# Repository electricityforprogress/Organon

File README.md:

# Organon
Biodata for Eurorack

This device can connect to the leaves of a plant and produces three pairs of Note CV and Gate signals, along with outputs for the 'raw' PWM Biodata square wave, a 'wiggly' CV output, and MIDI out!  The Organon comes with a set of snap electrode leads and three pairs of sticky pads. 
Using an Arduino Pro Micro 32u4, LMC555 timer, and a MC4728 Quad DAC this device was quite hard to find parts for until late 2023.

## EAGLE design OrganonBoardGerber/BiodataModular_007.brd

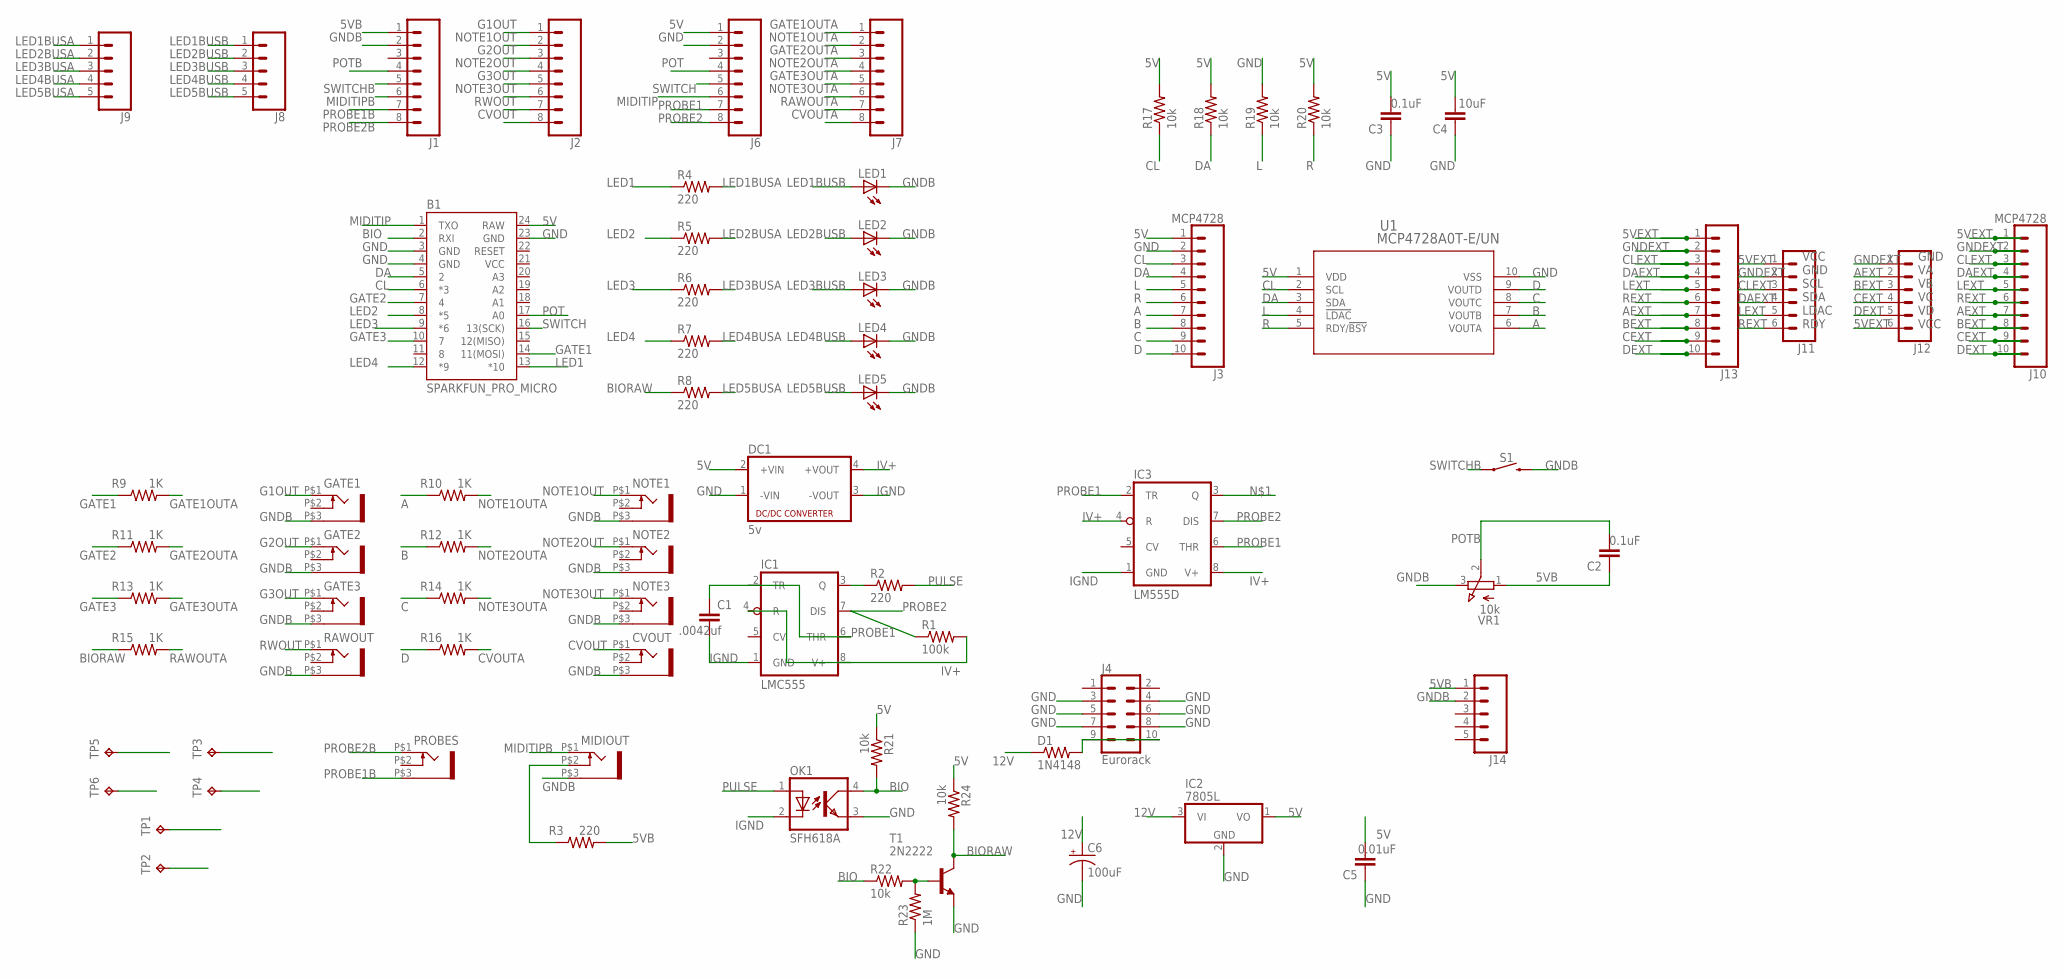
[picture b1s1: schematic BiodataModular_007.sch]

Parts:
B1: SPARKFUN_PRO_MICRO
C1: .0042uf; C2.5-2
C2, C3: 0.1uF; C2.5-2
C4: 10uF; C2.5-2
C5: 0.01uF; C2.5-2
C6: 100uF; B45181A
CVOUT: WQP-PJ301M-12_JACK
D1: 1N4148; 0204V
DC1: 5v; NME
GATE1, GATE2, GATE3: WQP-PJ301M-12_JACK
IC1: LMC555; DIL08
IC2: 7805L; TO92
IC3: LM555D; SO08
J1, J2, J6, J7: CONN_08"; 1X08
J3, J10: MCP4728; 1X10
J4: Eurorack; 2X5
J8, J9, J14: CONN_05; 1X05
J11, J12: CONN_06SILK_FEMALE_PTH; 1X06
J13: CONN_10SMD_MALE; 1X10_SMD_MALE
LED1, LED2, LED3, LED4, LED5: LED3MM
MIDIOUT: WQP-PJ301M-12_JACK
NOTE1, NOTE2, NOTE3: WQP-PJ301M-12_JACK
OK1: SFH618A; DIP4
PROBES: WQP-PJ301M-12_JACK
R1: 100k; 0204V
R2, R3, R4, R5, R6, R7, R8: 220; 0204V
R9, R10, R11, R12, R13, R14, R15, R16: 1K; 0204V
R17, R18, R19, R20, R21, R22, R24: 10k; 0204V
R23: 1M; 0204V
RAWOUT: WQP-PJ301M-12_JACK
S1: MOMENTARY-SWITCH-SPST-PTH-6.0MM; TACTILE_SWITCH_PTH_6.0MM
T1: 2N2222; TO92-EBC-OVAL
TP1, TP2, TP3, TP4, TP5, TP6: TPB1,27; B1,27
U1: MCP4728A0T-E/UN; MSOP10_MC
VR1: 10k; EVUF

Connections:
5V: B1.24 (RAW), C3.2, C4.2, C5.2, DC1.2 (+VIN), IC2.1 (VO), J3.1, J6.1, R17.2, R18.2, R20.2, R21.1, R24.1, U1.1 (VDD)
5VB: C2.1, J1.1, J14.1, R3.2, VR1.1 (A)
5VEXT: J10.1, J11.1, J12.6, J13.1
12V: C6.+, D1.1, IC2.3 (VI)
A: J3.7, R10.1, U1.6 (VOUTA)
AEXT: J10.7, J12.2, J13.7
B: J3.8, R12.1, U1.7 (VOUTB)
BEXT: J10.8, J12.3, J13.8
BIO: B1.2 (RXI), OK1.4 (COL), R21.2, R22.1
BIORAW: R8.1, R15.1, R24.2, T1.C
C: J3.9, R14.1, U1.8 (VOUTC)
CEXT: J10.9, J12.4, J13.9
CL: B1.6 (*3), J3.3, R17.1, U1.2 (SCL)
CLEXT: J10.3, J11.3, J13.3
CVOUT: CVOUT.P$1 (2), J2.8
CVOUTA: J7.8, R16.2
D: J3.10, R16.1, U1.9 (VOUTD)
DA: B1.5 (2), J3.4, R18.1, U1.3 (SDA)
DAEXT: J10.4, J11.4, J13.4
DEXT: J10.10, J12.5, J13.10
G1OUT: GATE1.P$1 (2), J2.1
G2OUT: GATE2.P$1 (2), J2.3
G3OUT: GATE3.P$1 (2), J2.5
GATE1: B1.14 (11(MOSI)), R9.1
GATE1OUTA: J7.1, R9.2
GATE2: B1.7 (4), R11.1
GATE2OUTA: J7.3, R11.2
GATE3: B1.10 (7), R13.1
GATE3OUTA: J7.5, R13.2
GND: B1.3 (GND), B1.4 (GND), B1.23 (GND), C3.1, C4.1, C5.1, C6.-, DC1.1 (-VIN), IC2.2 (GND), J3.2, J4.3, J4.4, J4.5, J4.6, J4.7, J4.8, J6.2, OK1.3 (EMIT), R19.2, R23.1, T1.E, U1.10 (VSS)
GNDB: CVOUT.P$3 (1), GATE1.P$3 (1), GATE2.P$3 (1), GATE3.P$3 (1), J1.2, J14.2, LED1.K (C), LED2.K (C), LED3.K (C), LED4.K (C), LED5.K (C), MIDIOUT.P$3 (1), NOTE1.P$3 (1), NOTE2.P$3 (1), NOTE3.P$3 (1), RAWOUT.P$3 (1), S1.3 (2), VR1.3 (E)
GNDEXT: J10.2, J11.2, J12.1, J13.2
IGND: C1.2, DC1.3 (-VOUT), IC1.1 (GND), IC3.1 (GND), OK1.2 (C)
IV+: DC1.4 (+VOUT), IC1.4 (R), IC1.8 (V+), IC3.4 (R), IC3.8 (V+), R1.2
L: J3.5, R19.1, U1.4 (!LDAC)
LED1: B1.13 (*10), R4.1
LED1BUSA: J9.1, R4.2
LED1BUSB: J8.1, LED1.A
LED2: B1.8 (*5), R5.1
LED2BUSA: J9.2, R5.2
LED2BUSB: J8.2, LED2.A
LED3: B1.9 (*6), R6.1
LED3BUSA: J9.3, R6.2
LED3BUSB: J8.3, LED3.A
LED4: B1.12 (*9), R7.1
LED4BUSA: J9.4, R7.2
LED4BUSB: J8.4, LED4.A
LED5BUSA: J9.5, R8.2
LED5BUSB: J8.5, LED5.A
LEXT: J10.5, J11.5, J13.5
MIDITIP: B1.1 (TXO), J6.6
MIDITIPB: J1.6, MIDIOUT.P$1 (2)
unnamed: IC1.3 (Q), IC3.3 (Q), R2.1
unnamed: MIDIOUT.P$2 (3), R3.1
unnamed: D1.2, J4.9, J4.10
unnamed: R22.2, R23.2, T1.B
NOTE1OUT: J2.2, NOTE1.P$1 (2)
NOTE1OUTA: J7.2, R10.2
NOTE2OUT: J2.4, NOTE2.P$1 (2)
NOTE2OUTA: J7.4, R12.2
NOTE3OUT: J2.6, NOTE3.P$1 (2)
NOTE3OUTA: J7.6, R14.2
POT: B1.17 (A0), J6.4
POTB: C2.2, J1.4, VR1.2 (S)
PROBE1: C1.1, IC1.2 (TR), IC1.6 (THR), IC3.2 (TR), IC3.6 (THR), J6.7
PROBE1B: J1.7, PROBES.P$3 (1), TP2.TP
PROBE1C: TP4.TP
PROBE1C1: TP6.TP
PROBE2: IC1.7 (DIS), IC3.7 (DIS), J6.8, R1.1
PROBE2B: J1.8, PROBES.P$1 (2), TP1.TP
PROBE2C: TP3.TP
PROBE2C1: TP5.TP
PULSE: OK1.1 (A), R2.2
R: J3.6, R20.1, U1.5 (RDY/!BSY)
RAWOUTA: J7.7, R15.2
REXT: J10.6, J11.6, J13.6
RWOUT: J2.7, RAWOUT.P$1 (2)
SWITCH: B1.16 (13(SCK)), J6.5
SWITCHB: J1.5, S1.1
VCC: B1.21 (VCC)

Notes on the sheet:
VCC GND SCL SDA LDAC RDY
GND VA VB VC VD VCC

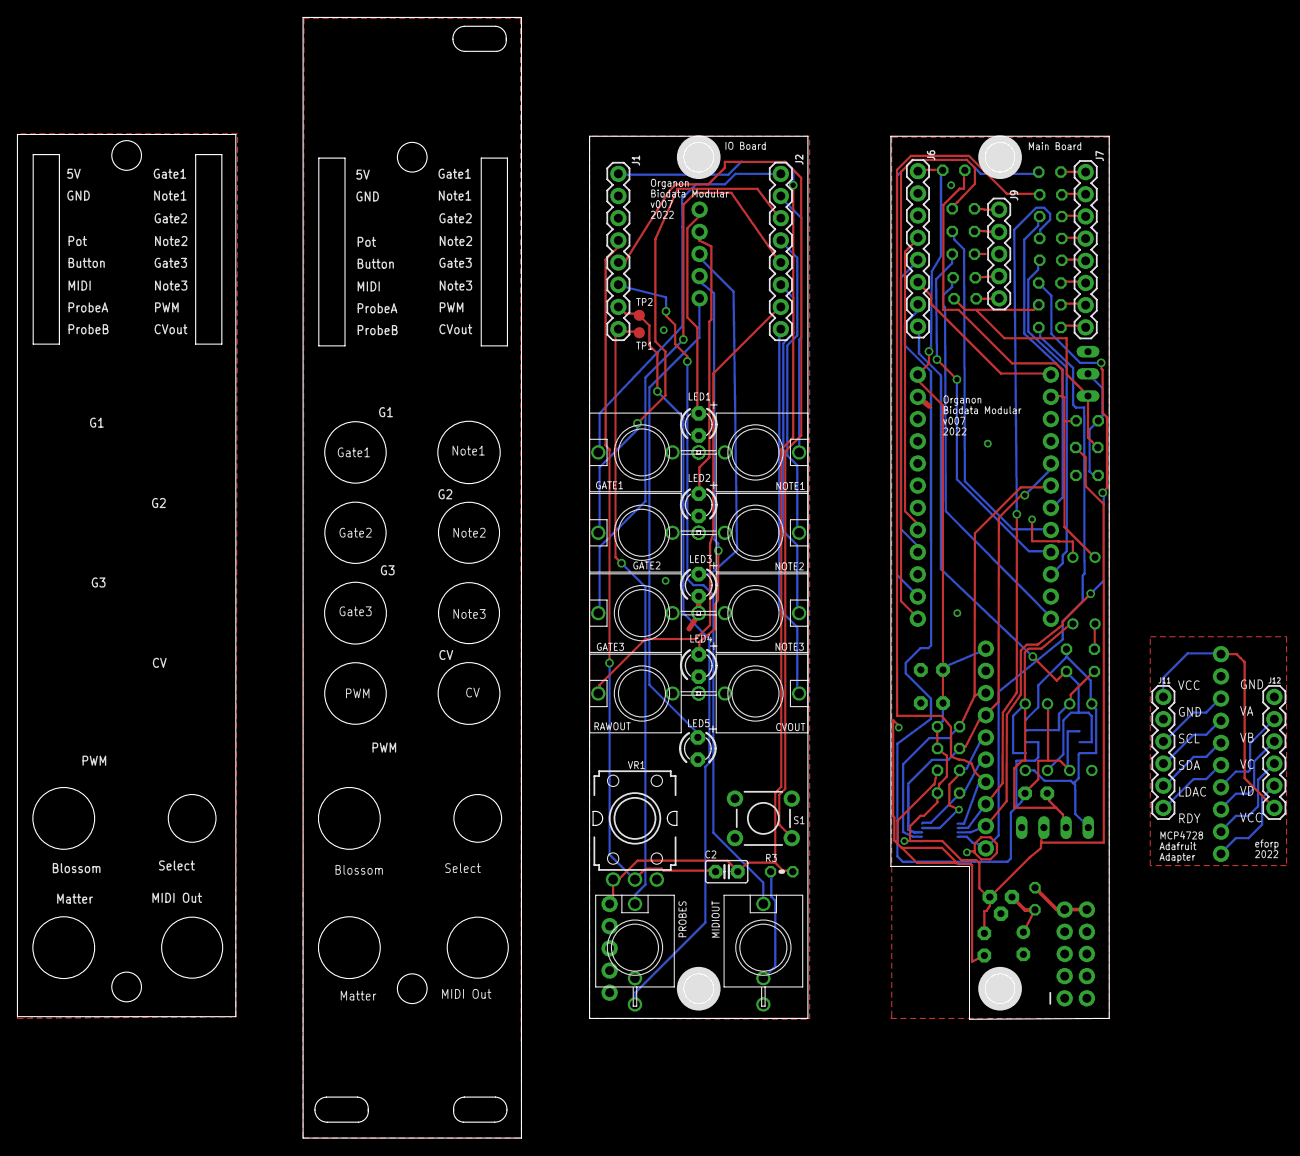
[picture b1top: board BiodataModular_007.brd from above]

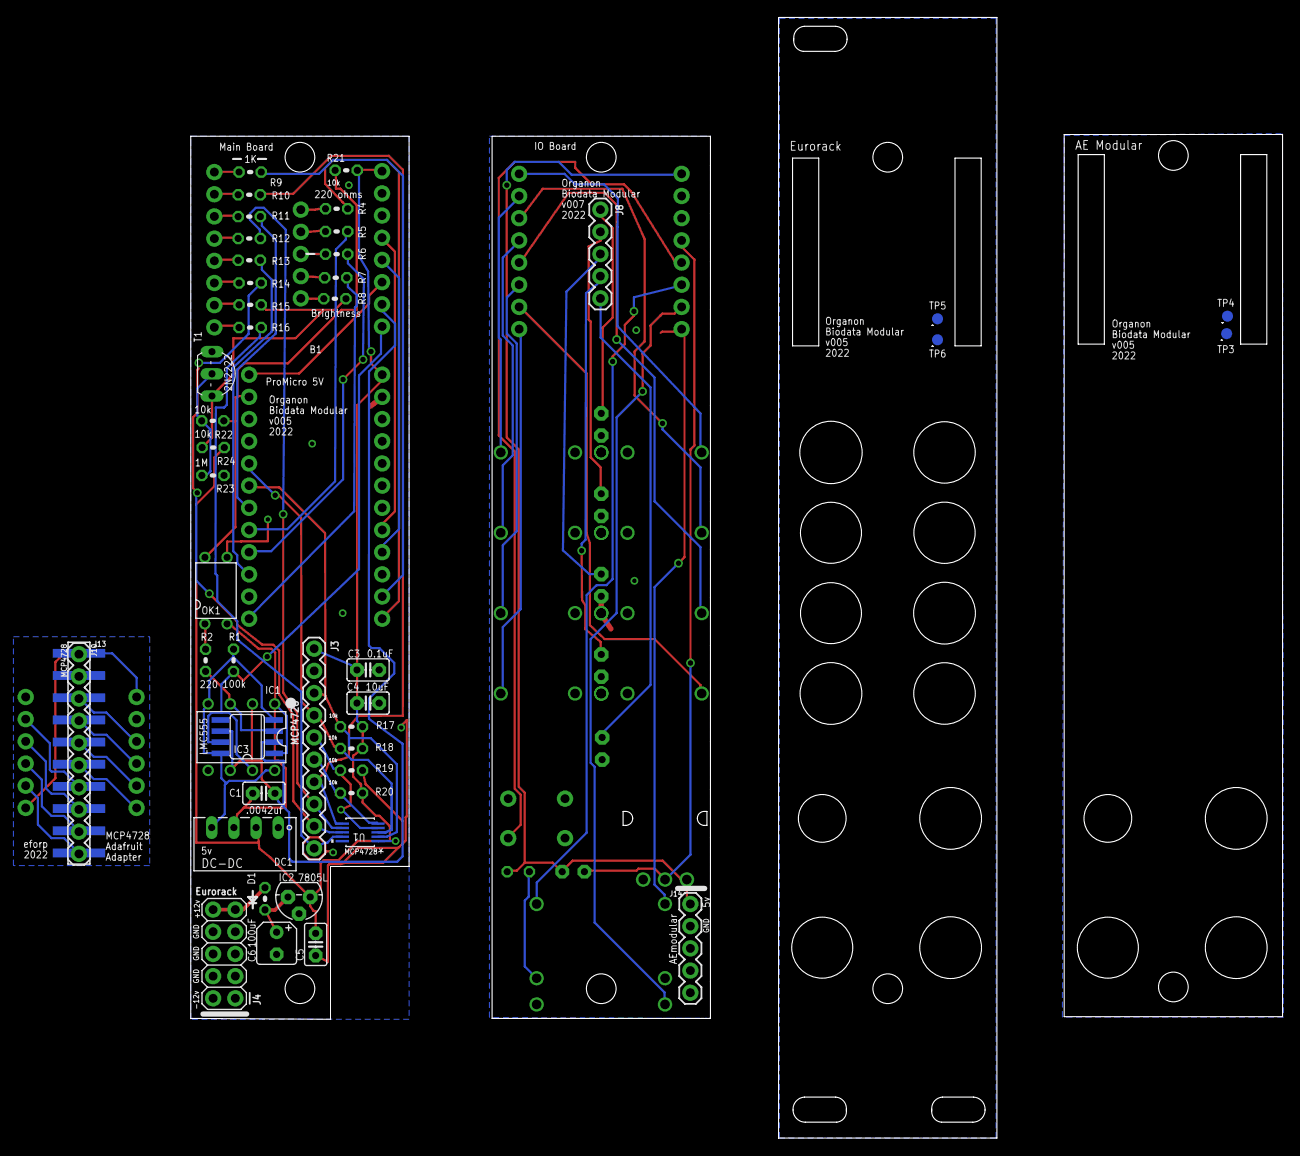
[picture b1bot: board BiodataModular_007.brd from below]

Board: 2 copper layers, 125.0 x 128.3 mm, 75 parts (47 on the bottom side), 75 nets.

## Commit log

2023-10-02 Gerber and Board files
    Hey it's open source, def try to make one if you want but please don't sell them or anything like that, thanks

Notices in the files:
parts and their libraries:
SparkFun-Switches: Licensing: Creative Commons ShareAlike 4.0 International - https://creativecommons.org/licenses/by-sa/4.0
